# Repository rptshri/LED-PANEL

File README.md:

# LED PANEL Gift created for gifting a friend.

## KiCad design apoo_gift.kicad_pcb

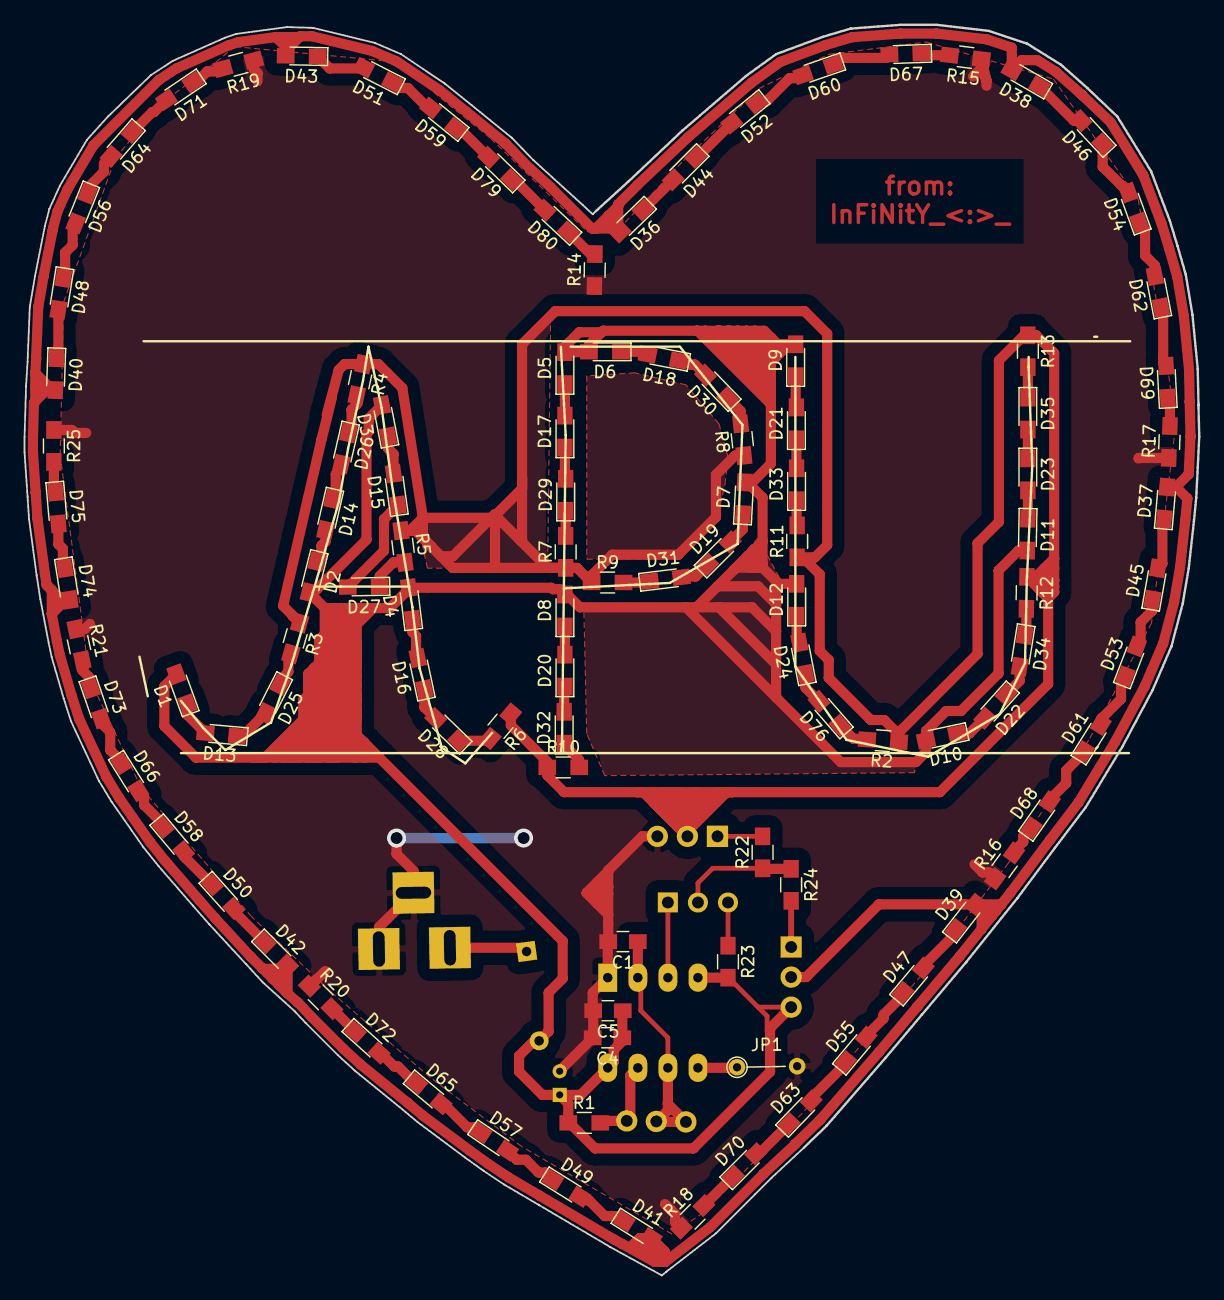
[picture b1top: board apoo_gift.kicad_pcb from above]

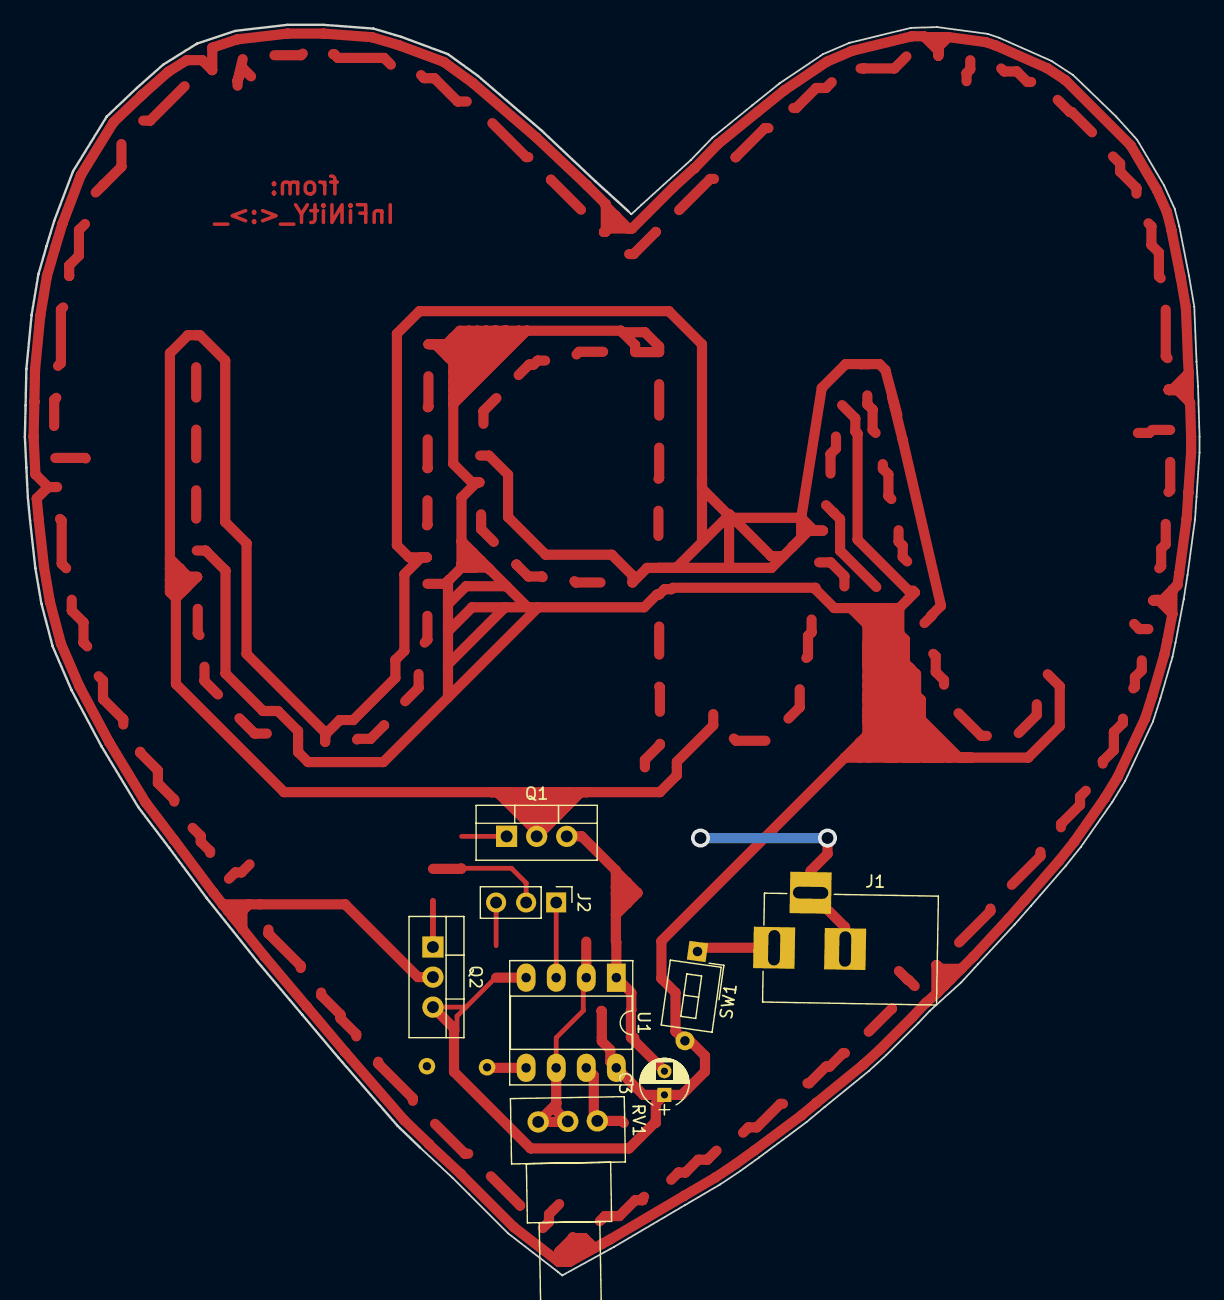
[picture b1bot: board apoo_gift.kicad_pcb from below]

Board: 2 copper layers, 99.2 x 105.6 mm, 115 parts (8 on the bottom side), 91 nets.

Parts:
C1: 10uF; C_0805_HandSoldering
C3: 10uF; CP_Radial_D4.0mm_P2.00mm
C4: .1uF; C_0805_HandSoldering
C5: 1uF; C_0805_HandSoldering
D1, D2, D3, D4, D5, D6, D7, D8, D9, D10, D11, D12, D13, D14, D15, D16, D17, D18, D19, D20, D21, D22, D23, D24, D25, D26, D27, D28, D29, D30, D31, D32, D33, D34, D35, D36, D37, D38, D39, D40, D41, D42, D43, D44, D45, D46, D47, D48, D49, D50, D51, D52, D53, D54, D55, D56, D57, D58, D59, D60, D61, D62, D63, D64, D65, D66, D67, D68, D69, D70, D71, D72, D73, D74, D75, D76, D79, D80: LED; LED_0805_HandSoldering
J1: Barrel_Jack_Switch; BARREL_JACK
J2: Conn_01x03_Male; Pin_Header_Straight_1x03_Pitch2.54mm
JP1: Jumper_NC_Small; R_Axial_DIN0204_L3.6mm_D1.6mm_P5.08mm_Vertical
Q1: TIP121; TO-220-3_Vertical
Q2: TIP126; TO-220-3_Vertical
R1, R2, R3, R4, R5, R6, R7, R8, R9, R10, R11, R12, R13, R14, R15, R16, R17, R18, R19, R20, R21, R23, R25: 1k; R_0805_HandSoldering
R22, R24: 510; R_0805_HandSoldering
RV1: 100k; Potentiometer_Alps_RK09Y_Vertical
SW1: SW_SPST; SW_DIP_x1_W7.62mm_Slide_LowProfile
U1: NE555; DIP-8_W7.62mm_Socket_LongPads

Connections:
/BLUE_LEDS: Q1.2, R2.1, R3.1, R4.1, R5.1, R6.1, R7.1, R8.1, R9.1, R10.1, R11.1, R12.1, R13.1
/RED_LEDS: D36.2, D37.2, D38.2, D39.2, D40.2, D41.2, D42.2, D43.2, D74.2, Q2.2
/SIGNAL: J2.2, R22.1, R24.1
/THR: C1.1, RV1.1, RV1.2, U1.2, U1.6
/out: J2.1, U1.3
GND: C1.2, C3.2, C4.2, C5.2, J1.2, J1.3, JP1.2, Q1.3, R14.1, R15.1, R16.1, R17.1, R18.1, R19.1, R20.1, R21.1, R25.1, U1.1
unnamed: D1.1, D13.2
unnamed: D10.1, D22.2
unnamed: D11.1, D23.2
unnamed: D12.1, D24.2
unnamed: D13.1, D25.2
unnamed: D14.1, D26.2
unnamed: D2.1, D14.2
unnamed: D15.1, D27.2
unnamed: D3.1, D15.2
unnamed: D16.1, D28.2
unnamed: D4.1, D16.2
unnamed: D17.1, D29.2
unnamed: D5.1, D17.2
unnamed: D18.1, D30.2
unnamed: D6.1, D18.2
unnamed: D19.1, D31.2
unnamed: D7.1, D19.2
unnamed: D20.1, D32.2
unnamed: D8.1, D20.2
unnamed: D21.1, D33.2
unnamed: D9.1, D21.2
unnamed: D22.1, D34.2
unnamed: D23.1, D35.2
unnamed: D24.1, D76.2
unnamed: D25.1, R3.2
unnamed: D26.1, R4.2
unnamed: D27.1, R5.2
unnamed: D28.1, R6.2
unnamed: D29.1, R7.2
unnamed: D30.1, R8.2
unnamed: D31.1, R9.2
unnamed: D32.1, R10.2
unnamed: D33.1, R11.2
unnamed: D34.1, R12.2
unnamed: D35.1, R13.2
unnamed: D36.1, D44.2
unnamed: D37.1, D45.2
unnamed: D38.1, D46.2
unnamed: D39.1, D47.2
unnamed: D40.1, D48.2
unnamed: D41.1, D49.2
unnamed: D42.1, D50.2
unnamed: D43.1, D51.2
unnamed: D44.1, D52.2
unnamed: D45.1, D53.2
unnamed: D46.1, D54.2
unnamed: D47.1, D55.2
unnamed: D48.1, D56.2
unnamed: D49.1, D57.2
unnamed: D50.1, D58.2
unnamed: D51.1, D59.2
unnamed: D52.1, D60.2
unnamed: D53.1, D61.2
unnamed: D54.1, D62.2
unnamed: D55.1, D63.2
unnamed: D56.1, D64.2
unnamed: D57.1, D65.2
unnamed: D58.1, D66.2
unnamed: D59.1, D79.2
unnamed: D60.1, D67.2
unnamed: D61.1, D68.2
unnamed: D62.1, D69.2
unnamed: D63.1, D70.2
unnamed: D64.1, D71.2
unnamed: D65.1, D72.2
unnamed: D66.1, D73.2
unnamed: D67.1, R15.2
unnamed: D68.1, R16.2
unnamed: D69.1, R17.2
unnamed: D70.1, R18.2
unnamed: D71.1, R19.2
unnamed: D72.1, R20.2
unnamed: D73.1, R21.2
unnamed: D74.1, D75.2
unnamed: D75.1, R25.2
unnamed: D76.1, R2.2
unnamed: D79.1, D80.2
unnamed: D80.1, R14.2
unnamed: J1.1, SW1.1
unnamed: J2.3, R23.1
unnamed: JP1.1, U1.5
unnamed: Q1.1, R22.2
unnamed: Q2.1, R24.2
unnamed: R1.2, RV1.3, U1.7
VCC: C3.1, C4.1, C5.1, D1.2, D2.2, D3.2, D4.2, D5.2, D6.2, D7.2, D8.2, D9.2, D10.2, D11.2, D12.2, Q2.3, R1.1, R23.2, SW1.2, U1.4, U1.8

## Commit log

2018-10-18 led panel
